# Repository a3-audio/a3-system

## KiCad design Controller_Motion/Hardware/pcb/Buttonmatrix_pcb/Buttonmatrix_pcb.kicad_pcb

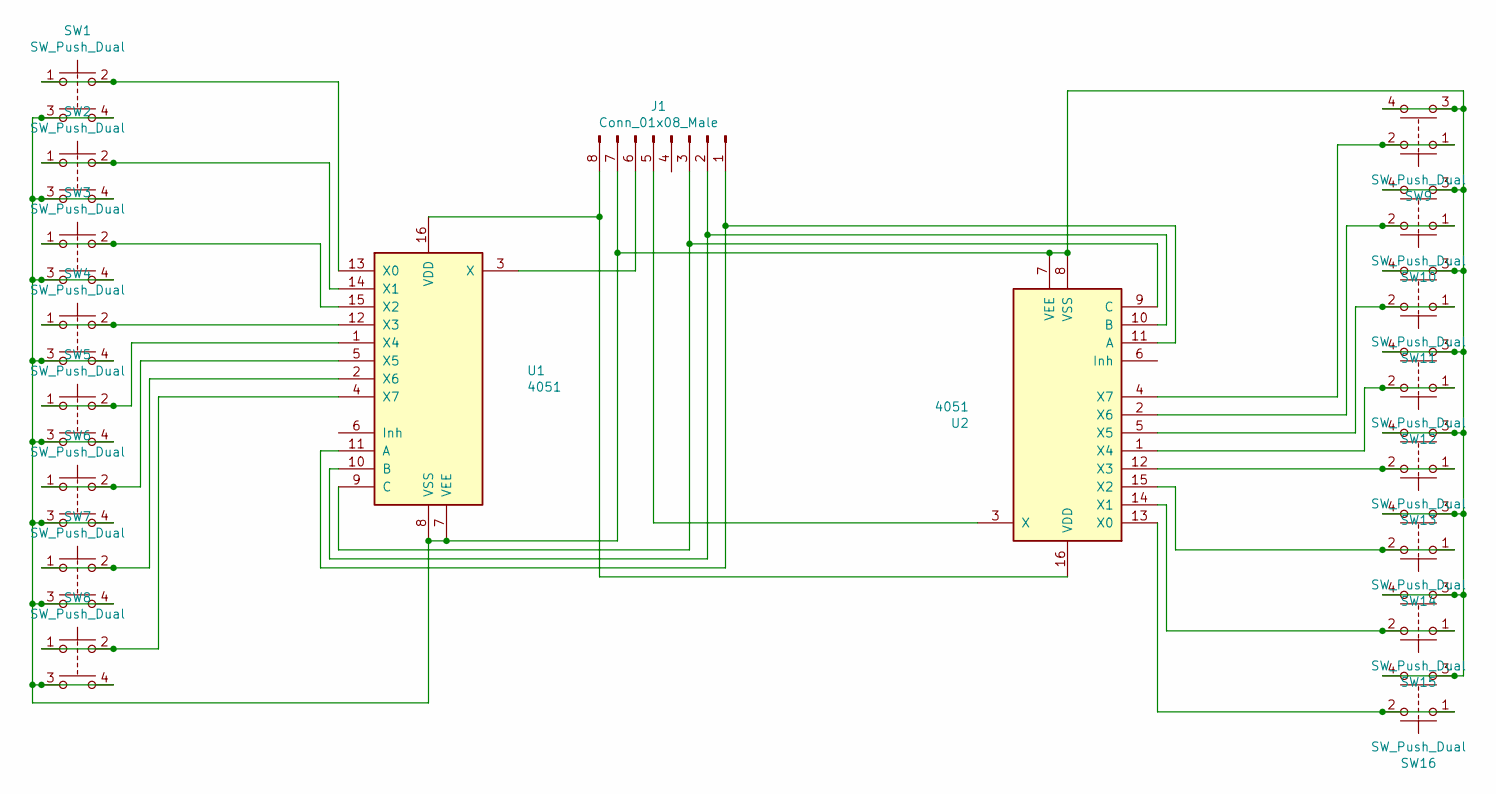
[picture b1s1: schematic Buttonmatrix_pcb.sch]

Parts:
J1: Conn_01x08_Male; IDC-Header_2x04_P2.54mm_Vertical
SW1, SW2, SW3, SW4, SW5, SW6, SW7, SW8, SW9, SW10, SW11, SW12, SW13, SW14, SW15, SW16: SW_Push_Dual; SW_PUSH-12mm
U1, U2: 4051; DIP-16_W7.62mm

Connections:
unnamed: J1.1, U1.11 (A), U2.11 (A)
unnamed: J1.2, U1.10 (B), U2.10 (B)
unnamed: J1.3, U1.9 (C), U2.9 (C)
unnamed: J1.5, U2.3 (X)
unnamed: J1.6, U1.3 (X)
unnamed: J1.7, SW1.3, SW1.4, SW2.3, SW2.4, SW3.3, SW3.4, SW4.3, SW4.4, SW5.3, SW5.4, SW6.3, SW6.4, SW7.3, SW7.4, SW8.3, SW8.4, SW9.3, SW9.4, SW10.3, SW10.4, SW11.3, SW11.4, SW12.3, SW12.4, SW13.3, SW13.4, SW14.3, SW14.4, SW15.3, SW15.4, SW16.3, SW16.4, U1.7 (VEE), U1.8 (VSS), U2.7 (VEE), U2.8 (VSS)
unnamed: J1.8, U1.16 (VDD), U2.16 (VDD)
unnamed: SW1.1, SW1.2, U1.13 (X0)
unnamed: SW2.1, SW2.2, U1.14 (X1)
unnamed: SW3.1, SW3.2, U1.15 (X2)
unnamed: SW4.1, SW4.2, U1.12 (X3)
unnamed: SW5.1, SW5.2, U1.1 (X4)
unnamed: SW6.1, SW6.2, U1.5 (X5)
unnamed: SW7.1, SW7.2, U1.2 (X6)
unnamed: SW8.1, SW8.2, U1.4 (X7)
unnamed: SW9.1, SW9.2, U2.4 (X7)
unnamed: SW10.1, SW10.2, U2.2 (X6)
unnamed: SW11.1, SW11.2, U2.5 (X5)
unnamed: SW12.1, SW12.2, U2.1 (X4)
unnamed: SW13.1, SW13.2, U2.12 (X3)
unnamed: SW14.1, SW14.2, U2.15 (X2)
unnamed: SW15.1, SW15.2, U2.14 (X1)
unnamed: SW16.1, SW16.2, U2.13 (X0)

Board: 2 copper layers, 19 parts (0 on the bottom side), 23 nets, no tracks yet.
